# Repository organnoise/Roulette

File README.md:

# Roulette

Roulette is a generative sequencer that uses probability algorithms to create rhythmically varied drum patterns. Compositionally the intent of Roulette is to enable its user to program drum patterns in a dynamic fashion, as opposed to the static nature of typical sequential composition. From the initial design of a rhythm, varied patterns are emitted outlining a principal musical form

## CAD
CAD files for 3D printing and CNC-ing

## Arduino 
Arduino code for Teeny++ 2.0

## Eagle

Designs for both the module and the shield pcbs.

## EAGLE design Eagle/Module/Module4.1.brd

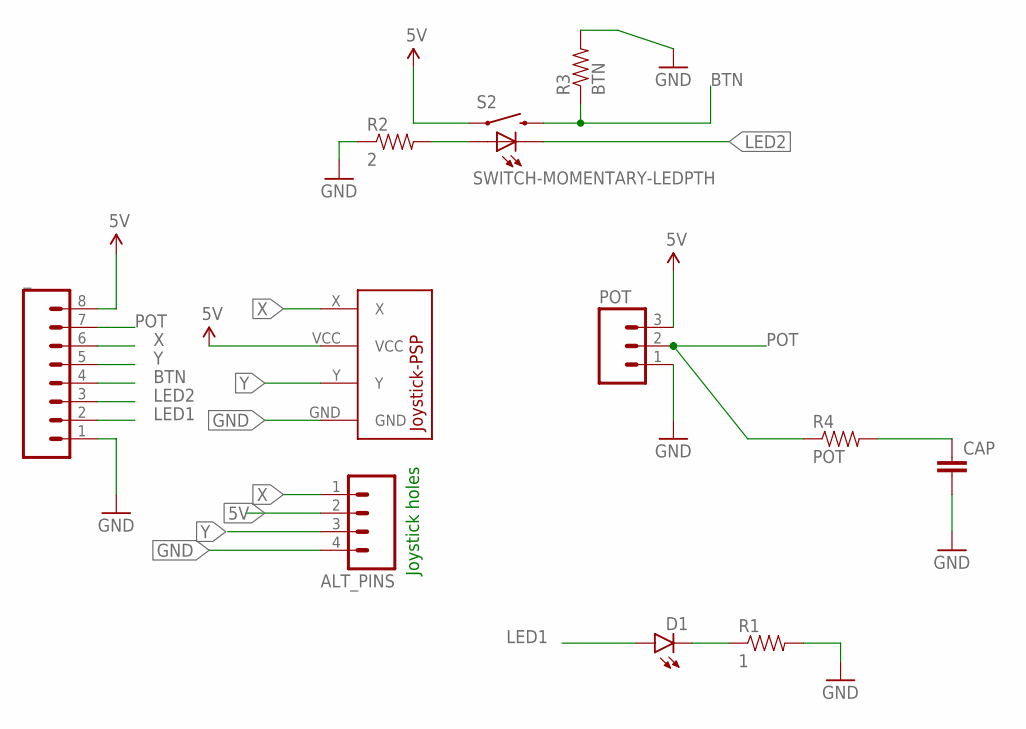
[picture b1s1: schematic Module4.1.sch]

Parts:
ALT_PINS: M04NO_SILK_ALL_ROUND; 1X04_NO_SILK_ALL_ROUND
CAP: CAPEZ; CAP-PTH-SMALLEZ
D1: LED3MM
POT: M031X03_NO_SILK; 1X03_NO_SILK
R1: 1; AXIAL-0.3-KIT
R2: 2; AXIAL-0.3-KIT
R3: BTN; AXIAL-0.3-KIT
R4: POT; AXIAL-0.3-KIT
S2: SWITCH-MOMENTARY-LEDPTH; TACTILE-PTH-LED-12MM
U$1: JOYSTICK-PSP1000
_: M08; 1X08_ROUND

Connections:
5V: ALT_PINS.2, POT.3, S2.4 (1), U$1.VCC, _.8
BTN: R3.P$1 (1), S2.2, _.4
GND: ALT_PINS.4, CAP.2, POT.1, R1.P$2 (2), R2.P$1 (1), R3.P$2 (2), U$1.GND, _.1
LED1: D1.A, _.2
LED2: S2.C, _.3
unnamed: D1.K (C), R1.P$1 (1)
unnamed: R2.P$2 (2), S2.A
unnamed: CAP.1, R4.P$2 (2)
POT: POT.2, R4.P$1 (1), _.7
X: ALT_PINS.1, U$1.X, _.6
Y: ALT_PINS.3, U$1.Y, _.5

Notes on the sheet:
Joystick holes

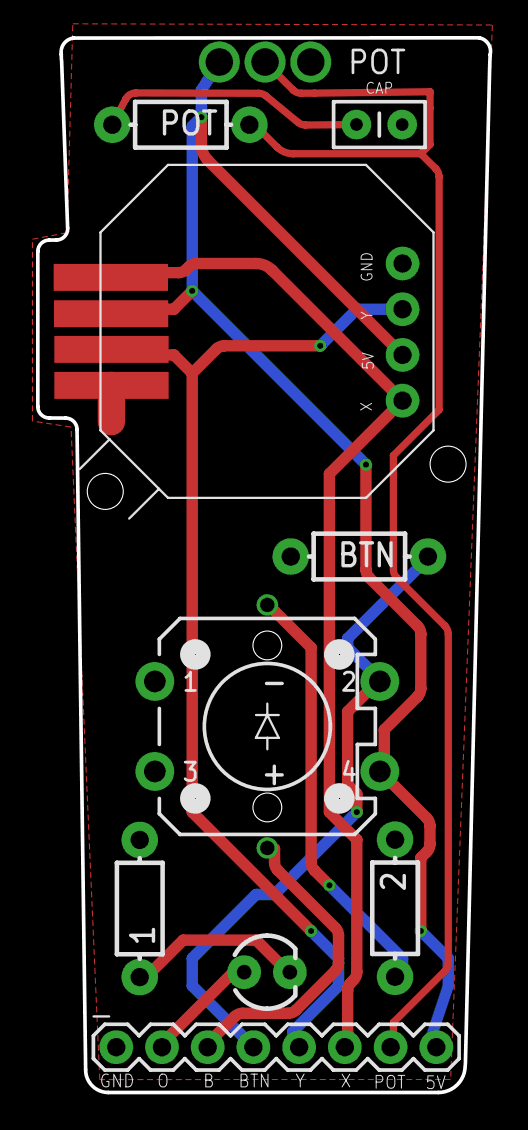
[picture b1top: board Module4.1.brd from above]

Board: 2 copper layers, 25.2 x 58.6 mm, 11 parts (0 on the bottom side), 11 nets.

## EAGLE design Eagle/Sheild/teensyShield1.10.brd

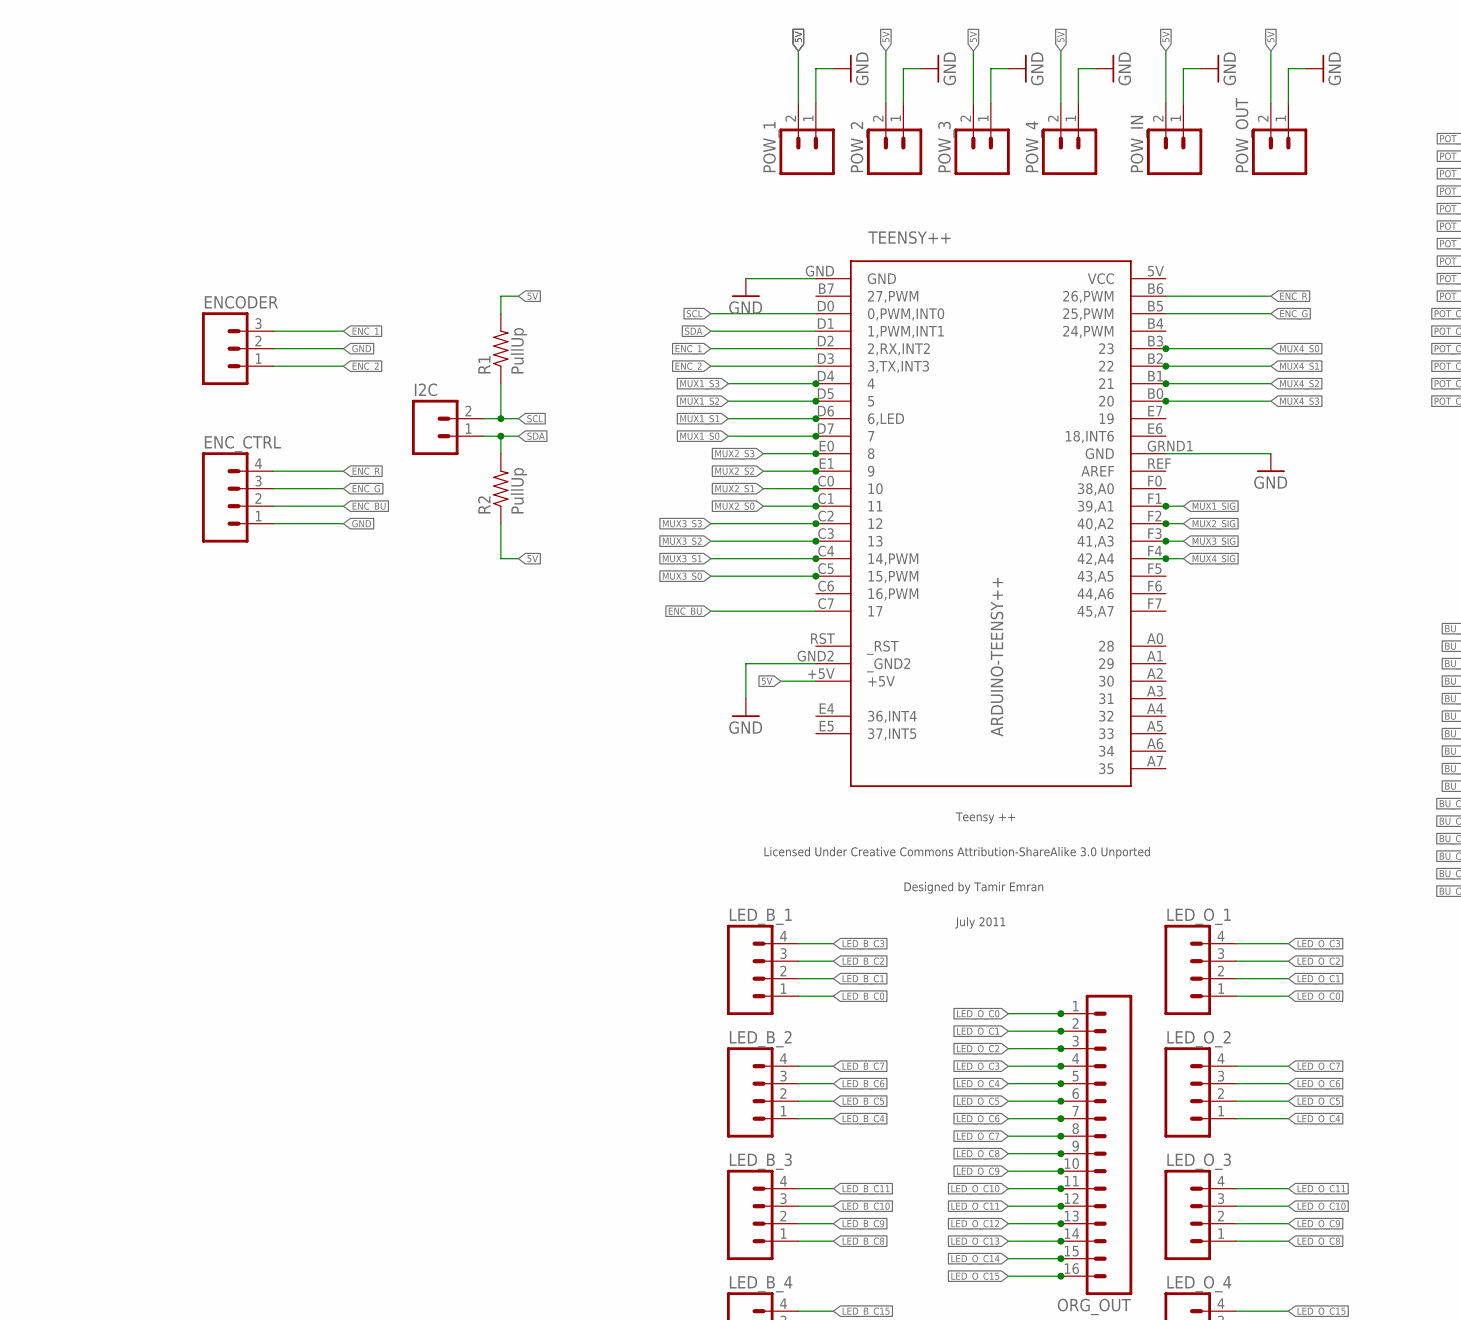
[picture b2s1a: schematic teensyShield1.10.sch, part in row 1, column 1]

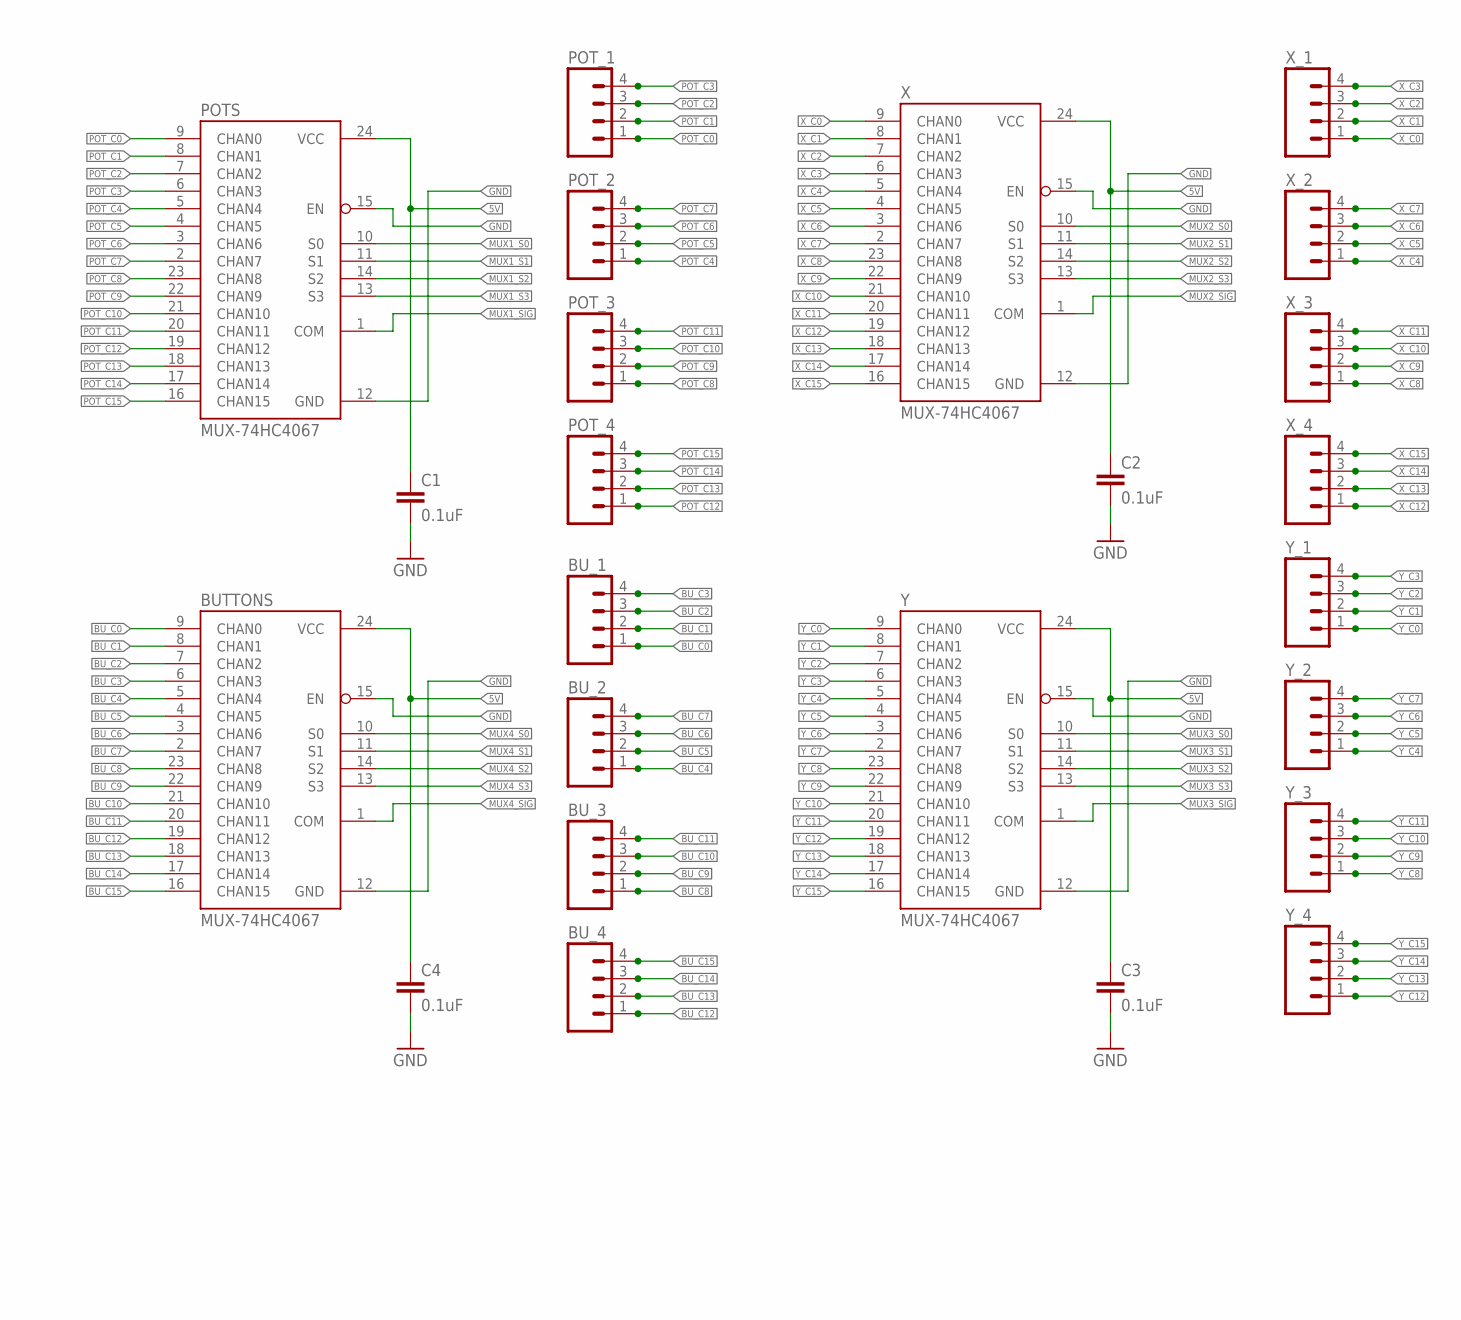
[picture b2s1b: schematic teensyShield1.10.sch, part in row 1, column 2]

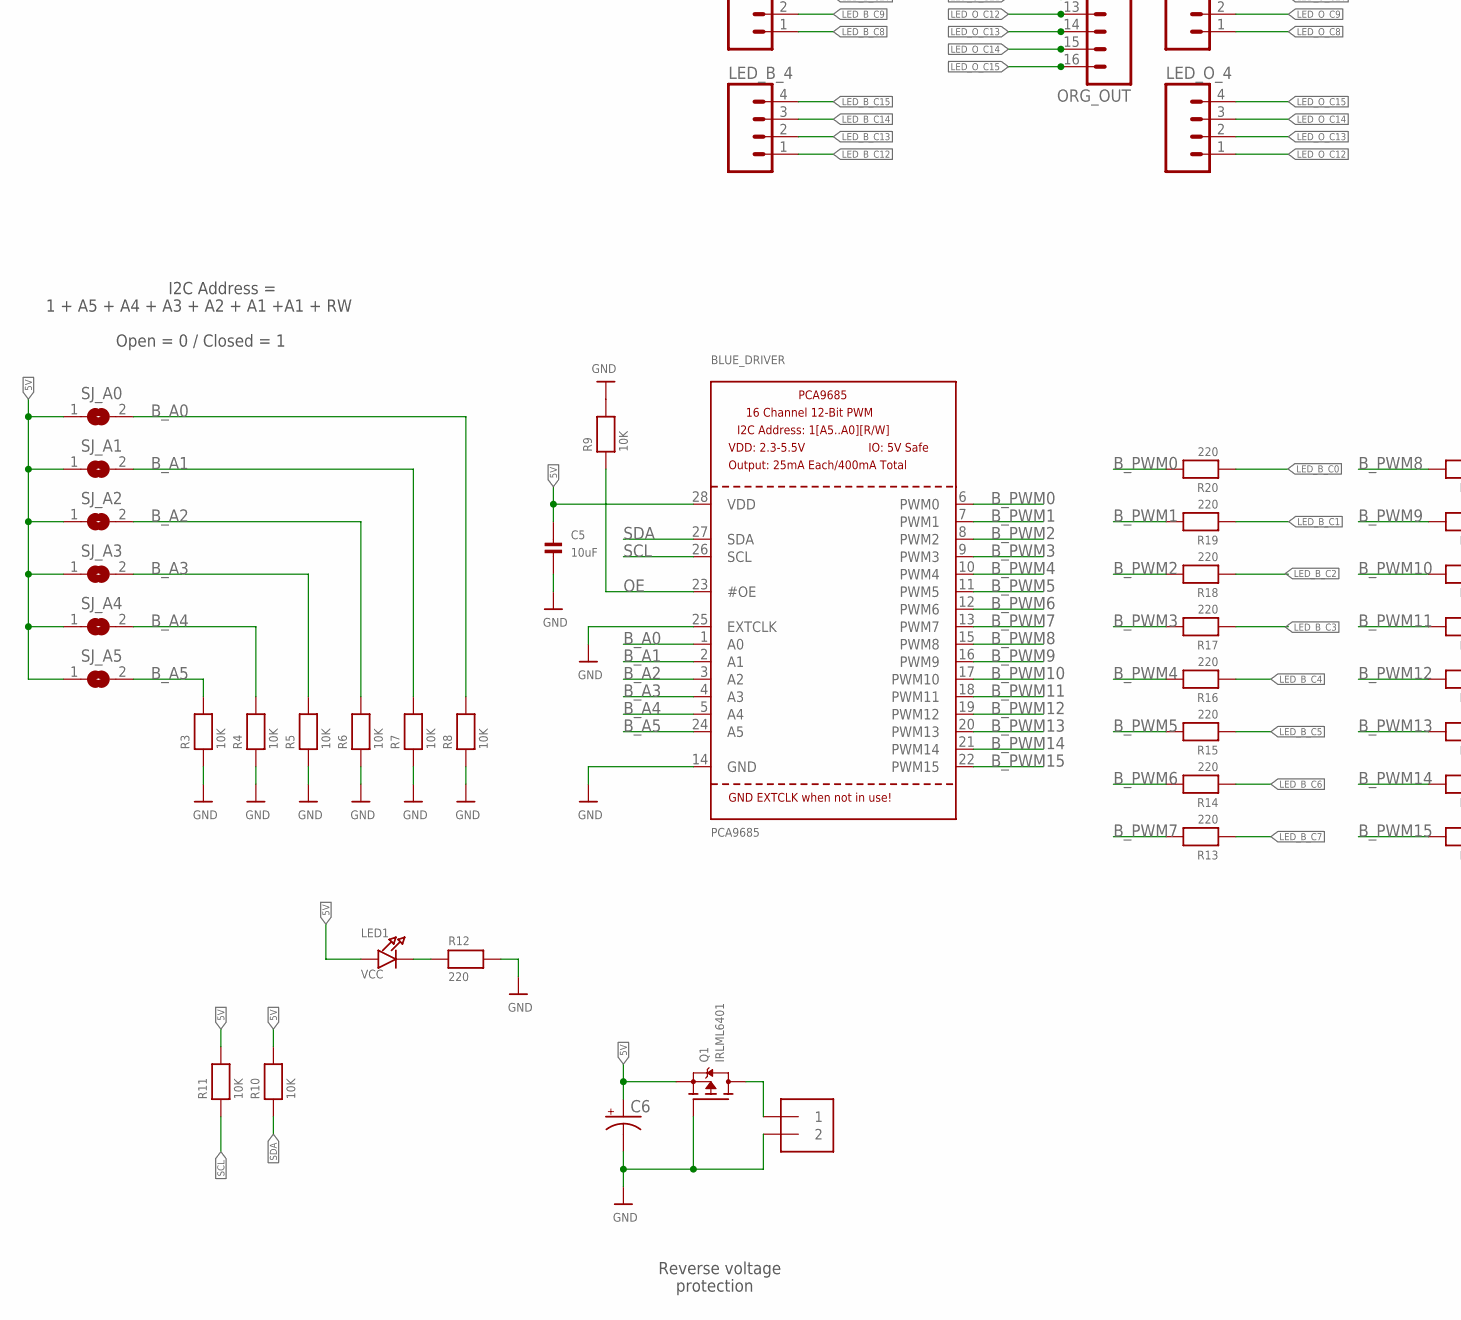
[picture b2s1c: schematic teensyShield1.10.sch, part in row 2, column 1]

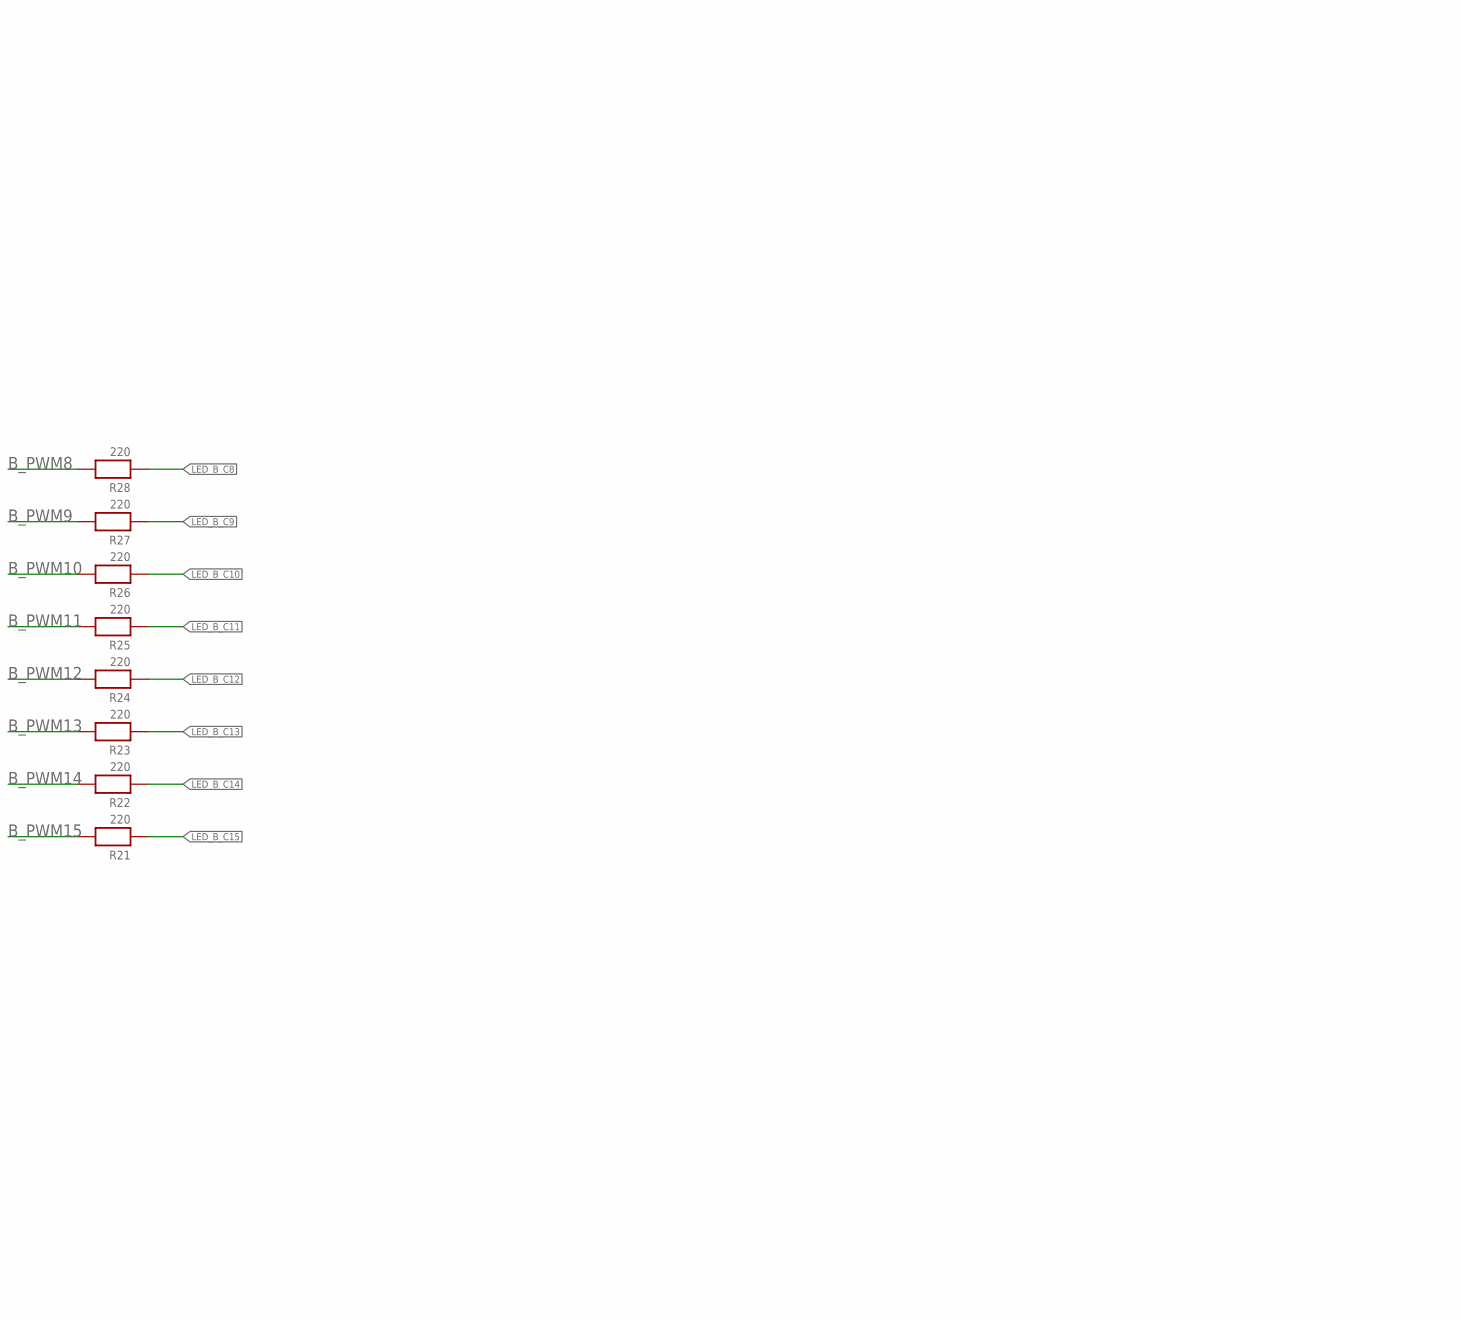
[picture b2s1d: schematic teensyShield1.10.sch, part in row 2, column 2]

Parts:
BLUE_DRIVER: PCA9685; TSSOP28
BUTTONS: MUX-74HC4067; SSOP24
BU_1, BU_2, BU_3, BU_4: M04NO_SILK_ALL_ROUND; 1X04_NO_SILK_ALL_ROUND
C1, C2, C3, C4: 0.1uF; 0603
C5: 10uF; 0805
C6: CPOL-USE3.5-8; E3,5-8
ENCODER: M031X03_NO_SILK; 1X03_NO_SILK
ENC_CTRL: M041X04_NO_SILK; 1X04_NO_SILK
I2C: M02LOCK; 1X02_LOCK
J1: TERMBLOCK_1X2-3.5MM; 1X2-3.5MM
LED1: VCC; CHIPLED_0805
LED_B_1, LED_B_2, LED_B_3, LED_B_4: M04NO_SILK_ALL_ROUND; 1X04_NO_SILK_ALL_ROUND
LED_O_1, LED_O_2, LED_O_3, LED_O_4: M04NO_SILK_ALL_ROUND; 1X04_NO_SILK_ALL_ROUND
ORG_OUT: M161X16_NO_SILK; 1X16_NO_SILK
POTS: MUX-74HC4067; SSOP24
POT_1, POT_2, POT_3, POT_4: M04NO_SILK_ALL_ROUND; 1X04_NO_SILK_ALL_ROUND
POW_1, POW_2, POW_3, POW_4: M02POLAR; MOLEX-1X2
POW_IN: M02POLAR; MOLEX-1X2
POW_OUT: M02POLAR; MOLEX-1X2
Q1: IRLML6401; SOT23-WIDE
R1, R2: PullUp; AXIAL-0.3
R3, R4, R5, R6, R7, R8, R9, R10, R11: 10K; 0805
R12, R13, R14, R15, R16, R17, R18, R19, R20, R21, R22, R23, R24, R25, R26, R27, R28: 220; 0805
SJ_A0, SJ_A1, SJ_A2, SJ_A3, SJ_A4, SJ_A5: SOLDERJUMPERREFLOW_NOPASTE; SOLDERJUMPER_REFLOW_NOPASTE
TEENSY++: ARDUINO-TEENSY++; TEENSY++
X: MUX-74HC4067; SSOP24
X_1, X_2, X_3, X_4: M04NO_SILK_ALL_ROUND; 1X04_NO_SILK_ALL_ROUND
Y: MUX-74HC4067; SSOP24
Y_1, Y_2, Y_3, Y_4: M04NO_SILK_ALL_ROUND; 1X04_NO_SILK_ALL_ROUND

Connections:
5V: BLUE_DRIVER.28 (VDD), BUTTONS.24 (VCC), C1.1, C2.1, C3.1, C4.1, C5.1, C6.+, LED1.A, POTS.24 (VCC), POW_1.2, POW_2.2, POW_3.2, POW_4.2, POW_IN.2, POW_OUT.2, Q1.2 (S), R1.P$2 (2), R2.P$1 (1), R10.2, R11.2, SJ_A0.1, SJ_A1.1, SJ_A2.1, SJ_A3.1, SJ_A4.1, SJ_A5.1, TEENSY++.+5V, X.24 (VCC), Y.24 (VCC)
BU_C0: BUTTONS.9 (CHAN0), BU_1.1
BU_C1: BUTTONS.8 (CHAN1), BU_1.2
BU_C2: BUTTONS.7 (CHAN2), BU_1.3
BU_C3: BUTTONS.6 (CHAN3), BU_1.4
BU_C4: BUTTONS.5 (CHAN4), BU_2.1
BU_C5: BUTTONS.4 (CHAN5), BU_2.2
BU_C6: BUTTONS.3 (CHAN6), BU_2.3
BU_C7: BUTTONS.2 (CHAN7), BU_2.4
BU_C8: BUTTONS.23 (CHAN8), BU_3.1
BU_C9: BUTTONS.22 (CHAN9), BU_3.2
BU_C10: BUTTONS.21 (CHAN10), BU_3.3
BU_C11: BUTTONS.20 (CHAN11), BU_3.4
BU_C12: BUTTONS.19 (CHAN12), BU_4.1
BU_C13: BUTTONS.18 (CHAN13), BU_4.2
BU_C14: BUTTONS.17 (CHAN14), BU_4.3
BU_C15: BUTTONS.16 (CHAN15), BU_4.4
B_A0: BLUE_DRIVER.1 (A0), R8.2, SJ_A0.2
B_A1: BLUE_DRIVER.2 (A1), R7.2, SJ_A1.2
B_A2: BLUE_DRIVER.3 (A2), R6.2, SJ_A2.2
B_A3: BLUE_DRIVER.4 (A3), R5.2, SJ_A3.2
B_A4: BLUE_DRIVER.5 (A4), R4.2, SJ_A4.2
B_A5: BLUE_DRIVER.24 (A5), R3.2, SJ_A5.2
B_PWM0: BLUE_DRIVER.6 (PWM0), R20.2
B_PWM1: BLUE_DRIVER.7 (PWM1), R19.2
B_PWM2: BLUE_DRIVER.8 (PWM2), R18.2
B_PWM3: BLUE_DRIVER.9 (PWM3), R17.2
B_PWM4: BLUE_DRIVER.10 (PWM4), R16.2
B_PWM5: BLUE_DRIVER.11 (PWM5), R15.2
B_PWM6: BLUE_DRIVER.12 (PWM6), R14.2
B_PWM7: BLUE_DRIVER.13 (PWM7), R13.2
B_PWM8: BLUE_DRIVER.15 (PWM8), R28.2
B_PWM9: BLUE_DRIVER.16 (PWM9), R27.2
B_PWM10: BLUE_DRIVER.17 (PWM10), R26.2
B_PWM11: BLUE_DRIVER.18 (PWM11), R25.2
B_PWM12: BLUE_DRIVER.19 (PWM12), R24.2
B_PWM13: BLUE_DRIVER.20 (PWM13), R23.2
B_PWM14: BLUE_DRIVER.21 (PWM14), R22.2
B_PWM15: BLUE_DRIVER.22 (PWM15), R21.2
ENC_1: ENCODER.3, TEENSY++.D2 (2,RX,INT2)
ENC_2: ENCODER.1, TEENSY++.D3 (3,TX,INT3)
ENC_BU: ENC_CTRL.2, TEENSY++.C7 (17)
ENC_G: ENC_CTRL.3, TEENSY++.B5 (25,PWM)
ENC_R: ENC_CTRL.4, TEENSY++.B6 (26,PWM)
GND: BLUE_DRIVER.14 (GND), BLUE_DRIVER.25 (EXTCLK), BUTTONS.12 (GND), BUTTONS.15 (EN), C1.2, C2.2, C3.2, C4.2, C5.2, C6.-, ENCODER.2, ENC_CTRL.1, J1.2, POTS.12 (GND), POTS.15 (EN), POW_1.1, POW_2.1, POW_3.1, POW_4.1, POW_IN.1, POW_OUT.1, Q1.1 (G), R3.1, R4.1, R5.1, R6.1, R7.1, R8.1, R9.2, R12.2, TEENSY++.GND, TEENSY++.GND2 (_GND2), TEENSY++.GRND1 (GND), X.12 (GND), X.15 (EN), Y.12 (GND), Y.15 (EN)
LED_B_C0: LED_B_1.1, R20.1
LED_B_C1: LED_B_1.2, R19.1
LED_B_C2: LED_B_1.3, R18.1
LED_B_C3: LED_B_1.4, R17.1
LED_B_C4: LED_B_2.1, R16.1
LED_B_C5: LED_B_2.2, R15.1
LED_B_C6: LED_B_2.3, R14.1
LED_B_C7: LED_B_2.4, R13.1
LED_B_C8: LED_B_3.1, R28.1
LED_B_C9: LED_B_3.2, R27.1
LED_B_C10: LED_B_3.3, R26.1
LED_B_C11: LED_B_3.4, R25.1
LED_B_C12: LED_B_4.1, R24.1
LED_B_C13: LED_B_4.2, R23.1
LED_B_C14: LED_B_4.3, R22.1
LED_B_C15: LED_B_4.4, R21.1
LED_O_C0: LED_O_1.1, ORG_OUT.1
LED_O_C1: LED_O_1.2, ORG_OUT.2
LED_O_C2: LED_O_1.3, ORG_OUT.3
LED_O_C3: LED_O_1.4, ORG_OUT.4
LED_O_C4: LED_O_2.1, ORG_OUT.5
LED_O_C5: LED_O_2.2, ORG_OUT.6
LED_O_C6: LED_O_2.3, ORG_OUT.7
LED_O_C7: LED_O_2.4, ORG_OUT.8
LED_O_C8: LED_O_3.1, ORG_OUT.9
LED_O_C9: LED_O_3.2, ORG_OUT.10
LED_O_C10: LED_O_3.3, ORG_OUT.11
LED_O_C11: LED_O_3.4, ORG_OUT.12
LED_O_C12: LED_O_4.1, ORG_OUT.13
LED_O_C13: LED_O_4.2, ORG_OUT.14
LED_O_C14: LED_O_4.3, ORG_OUT.15
LED_O_C15: LED_O_4.4, ORG_OUT.16
MUX1_S0: POTS.10 (S0), TEENSY++.D7 (7)
MUX1_S1: POTS.11 (S1), TEENSY++.D6 (6,LED)
MUX1_S2: POTS.14 (S2), TEENSY++.D5 (5)
MUX1_S3: POTS.13 (S3), TEENSY++.D4 (4)
MUX1_SIG: POTS.1 (COM), TEENSY++.F1 (39,A1)
MUX2_S0: TEENSY++.C1 (11), X.10 (S0)
MUX2_S1: TEENSY++.C0 (10), X.11 (S1)
MUX2_S2: TEENSY++.E1 (9), X.14 (S2)
MUX2_S3: TEENSY++.E0 (8), X.13 (S3)
MUX2_SIG: TEENSY++.F2 (40,A2), X.1 (COM)
MUX3_S0: TEENSY++.C5 (15,PWM), Y.10 (S0)
MUX3_S1: TEENSY++.C4 (14,PWM), Y.11 (S1)
MUX3_S2: TEENSY++.C3 (13), Y.14 (S2)
MUX3_S3: TEENSY++.C2 (12), Y.13 (S3)
MUX3_SIG: TEENSY++.F3 (41,A3), Y.1 (COM)
MUX4_S0: BUTTONS.10 (S0), TEENSY++.B3 (23)
MUX4_S1: BUTTONS.11 (S1), TEENSY++.B2 (22)
MUX4_S2: BUTTONS.14 (S2), TEENSY++.B1 (21)
MUX4_S3: BUTTONS.13 (S3), TEENSY++.B0 (20)
MUX4_SIG: BUTTONS.1 (COM), TEENSY++.F4 (42,A4)
unnamed: LED1.C, R12.1
OE: BLUE_DRIVER.23 (#OE), R9.1
POT_C0: POTS.9 (CHAN0), POT_1.1
POT_C1: POTS.8 (CHAN1), POT_1.2
POT_C2: POTS.7 (CHAN2), POT_1.3
POT_C3: POTS.6 (CHAN3), POT_1.4
POT_C4: POTS.5 (CHAN4), POT_2.1
POT_C5: POTS.4 (CHAN5), POT_2.2
POT_C6: POTS.3 (CHAN6), POT_2.3
POT_C7: POTS.2 (CHAN7), POT_2.4
POT_C8: POTS.23 (CHAN8), POT_3.1
POT_C9: POTS.22 (CHAN9), POT_3.2
POT_C10: POTS.21 (CHAN10), POT_3.3
POT_C11: POTS.20 (CHAN11), POT_3.4
POT_C12: POTS.19 (CHAN12), POT_4.1
POT_C13: POTS.18 (CHAN13), POT_4.2
POT_C14: POTS.17 (CHAN14), POT_4.3
POT_C15: POTS.16 (CHAN15), POT_4.4
PWRIN: J1.1, Q1.3 (D)
SCL: BLUE_DRIVER.26 (SCL), I2C.2, R1.P$1 (1), R11.1, TEENSY++.D0 (0,PWM,INT0)
SDA: BLUE_DRIVER.27 (SDA), I2C.1, R2.P$2 (2), R10.1, TEENSY++.D1 (1,PWM,INT1)
VCC: TEENSY++.5V (VCC)
X_C0: X.9 (CHAN0), X_1.1
X_C1: X.8 (CHAN1), X_1.2
X_C2: X.7 (CHAN2), X_1.3
X_C3: X.6 (CHAN3), X_1.4
X_C4: X.5 (CHAN4), X_2.1
X_C5: X.4 (CHAN5), X_2.2
X_C6: X.3 (CHAN6), X_2.3
X_C7: X.2 (CHAN7), X_2.4
X_C8: X.23 (CHAN8), X_3.1
X_C9: X.22 (CHAN9), X_3.2
X_C10: X.21 (CHAN10), X_3.3
X_C11: X.20 (CHAN11), X_3.4
X_C12: X.19 (CHAN12), X_4.1
X_C13: X.18 (CHAN13), X_4.2
X_C14: X.17 (CHAN14), X_4.3
X_C15: X.16 (CHAN15), X_4.4
Y_C0: Y.9 (CHAN0), Y_1.1
Y_C1: Y.8 (CHAN1), Y_1.2
Y_C2: Y.7 (CHAN2), Y_1.3
Y_C3: Y.6 (CHAN3), Y_1.4
Y_C4: Y.5 (CHAN4), Y_2.1
Y_C5: Y.4 (CHAN5), Y_2.2
Y_C6: Y.3 (CHAN6), Y_2.3
Y_C7: Y.2 (CHAN7), Y_2.4
Y_C8: Y.23 (CHAN8), Y_3.1
Y_C9: Y.22 (CHAN9), Y_3.2
Y_C10: Y.21 (CHAN10), Y_3.3
Y_C11: Y.20 (CHAN11), Y_3.4
Y_C12: Y.19 (CHAN12), Y_4.1
Y_C13: Y.18 (CHAN13), Y_4.2
Y_C14: Y.17 (CHAN14), Y_4.3
Y_C15: Y.16 (CHAN15), Y_4.4

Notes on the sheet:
Reverse voltage
protection
1 + A5 + A4 + A3 + A2 + A1 +A1 + RW
I2C Address =
Open = 0 / Closed = 1

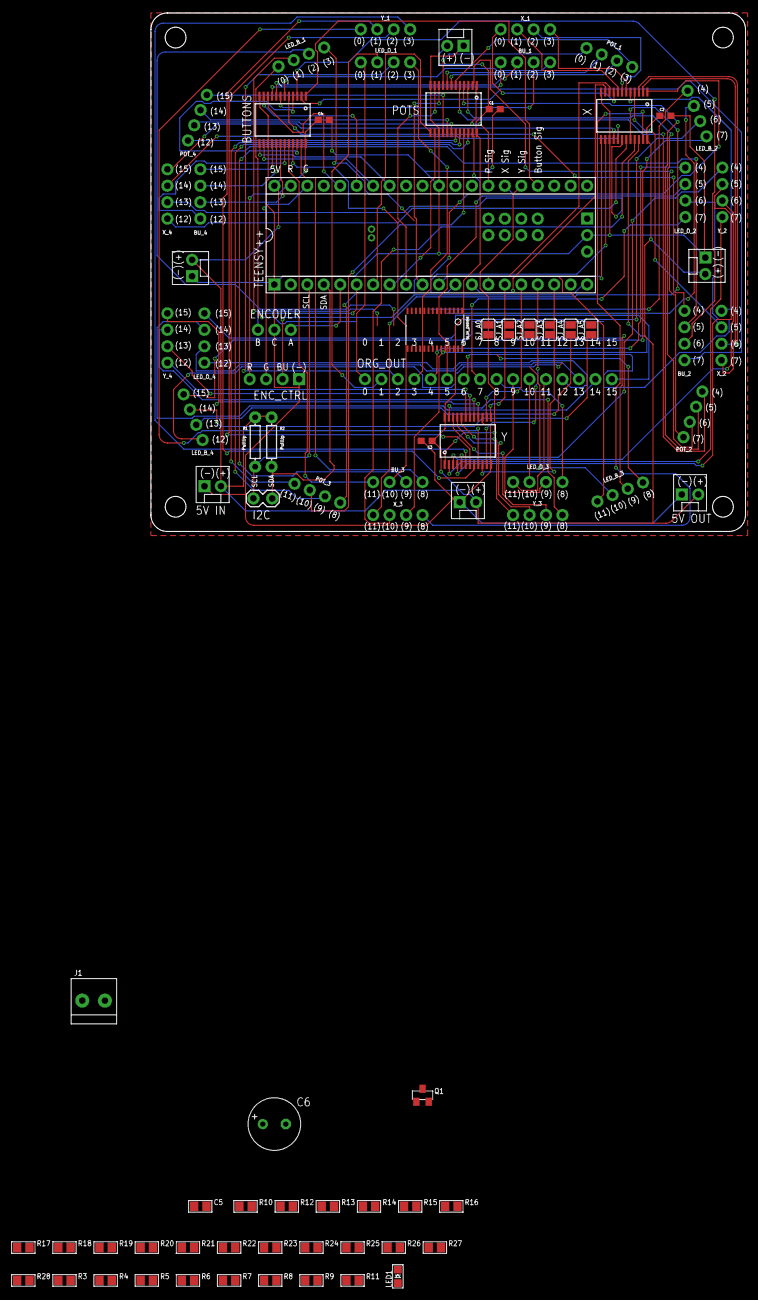
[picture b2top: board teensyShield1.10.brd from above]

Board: 2 copper layers, 91.7 x 80.0 mm, 83 parts (0 on the bottom side), 150 nets.

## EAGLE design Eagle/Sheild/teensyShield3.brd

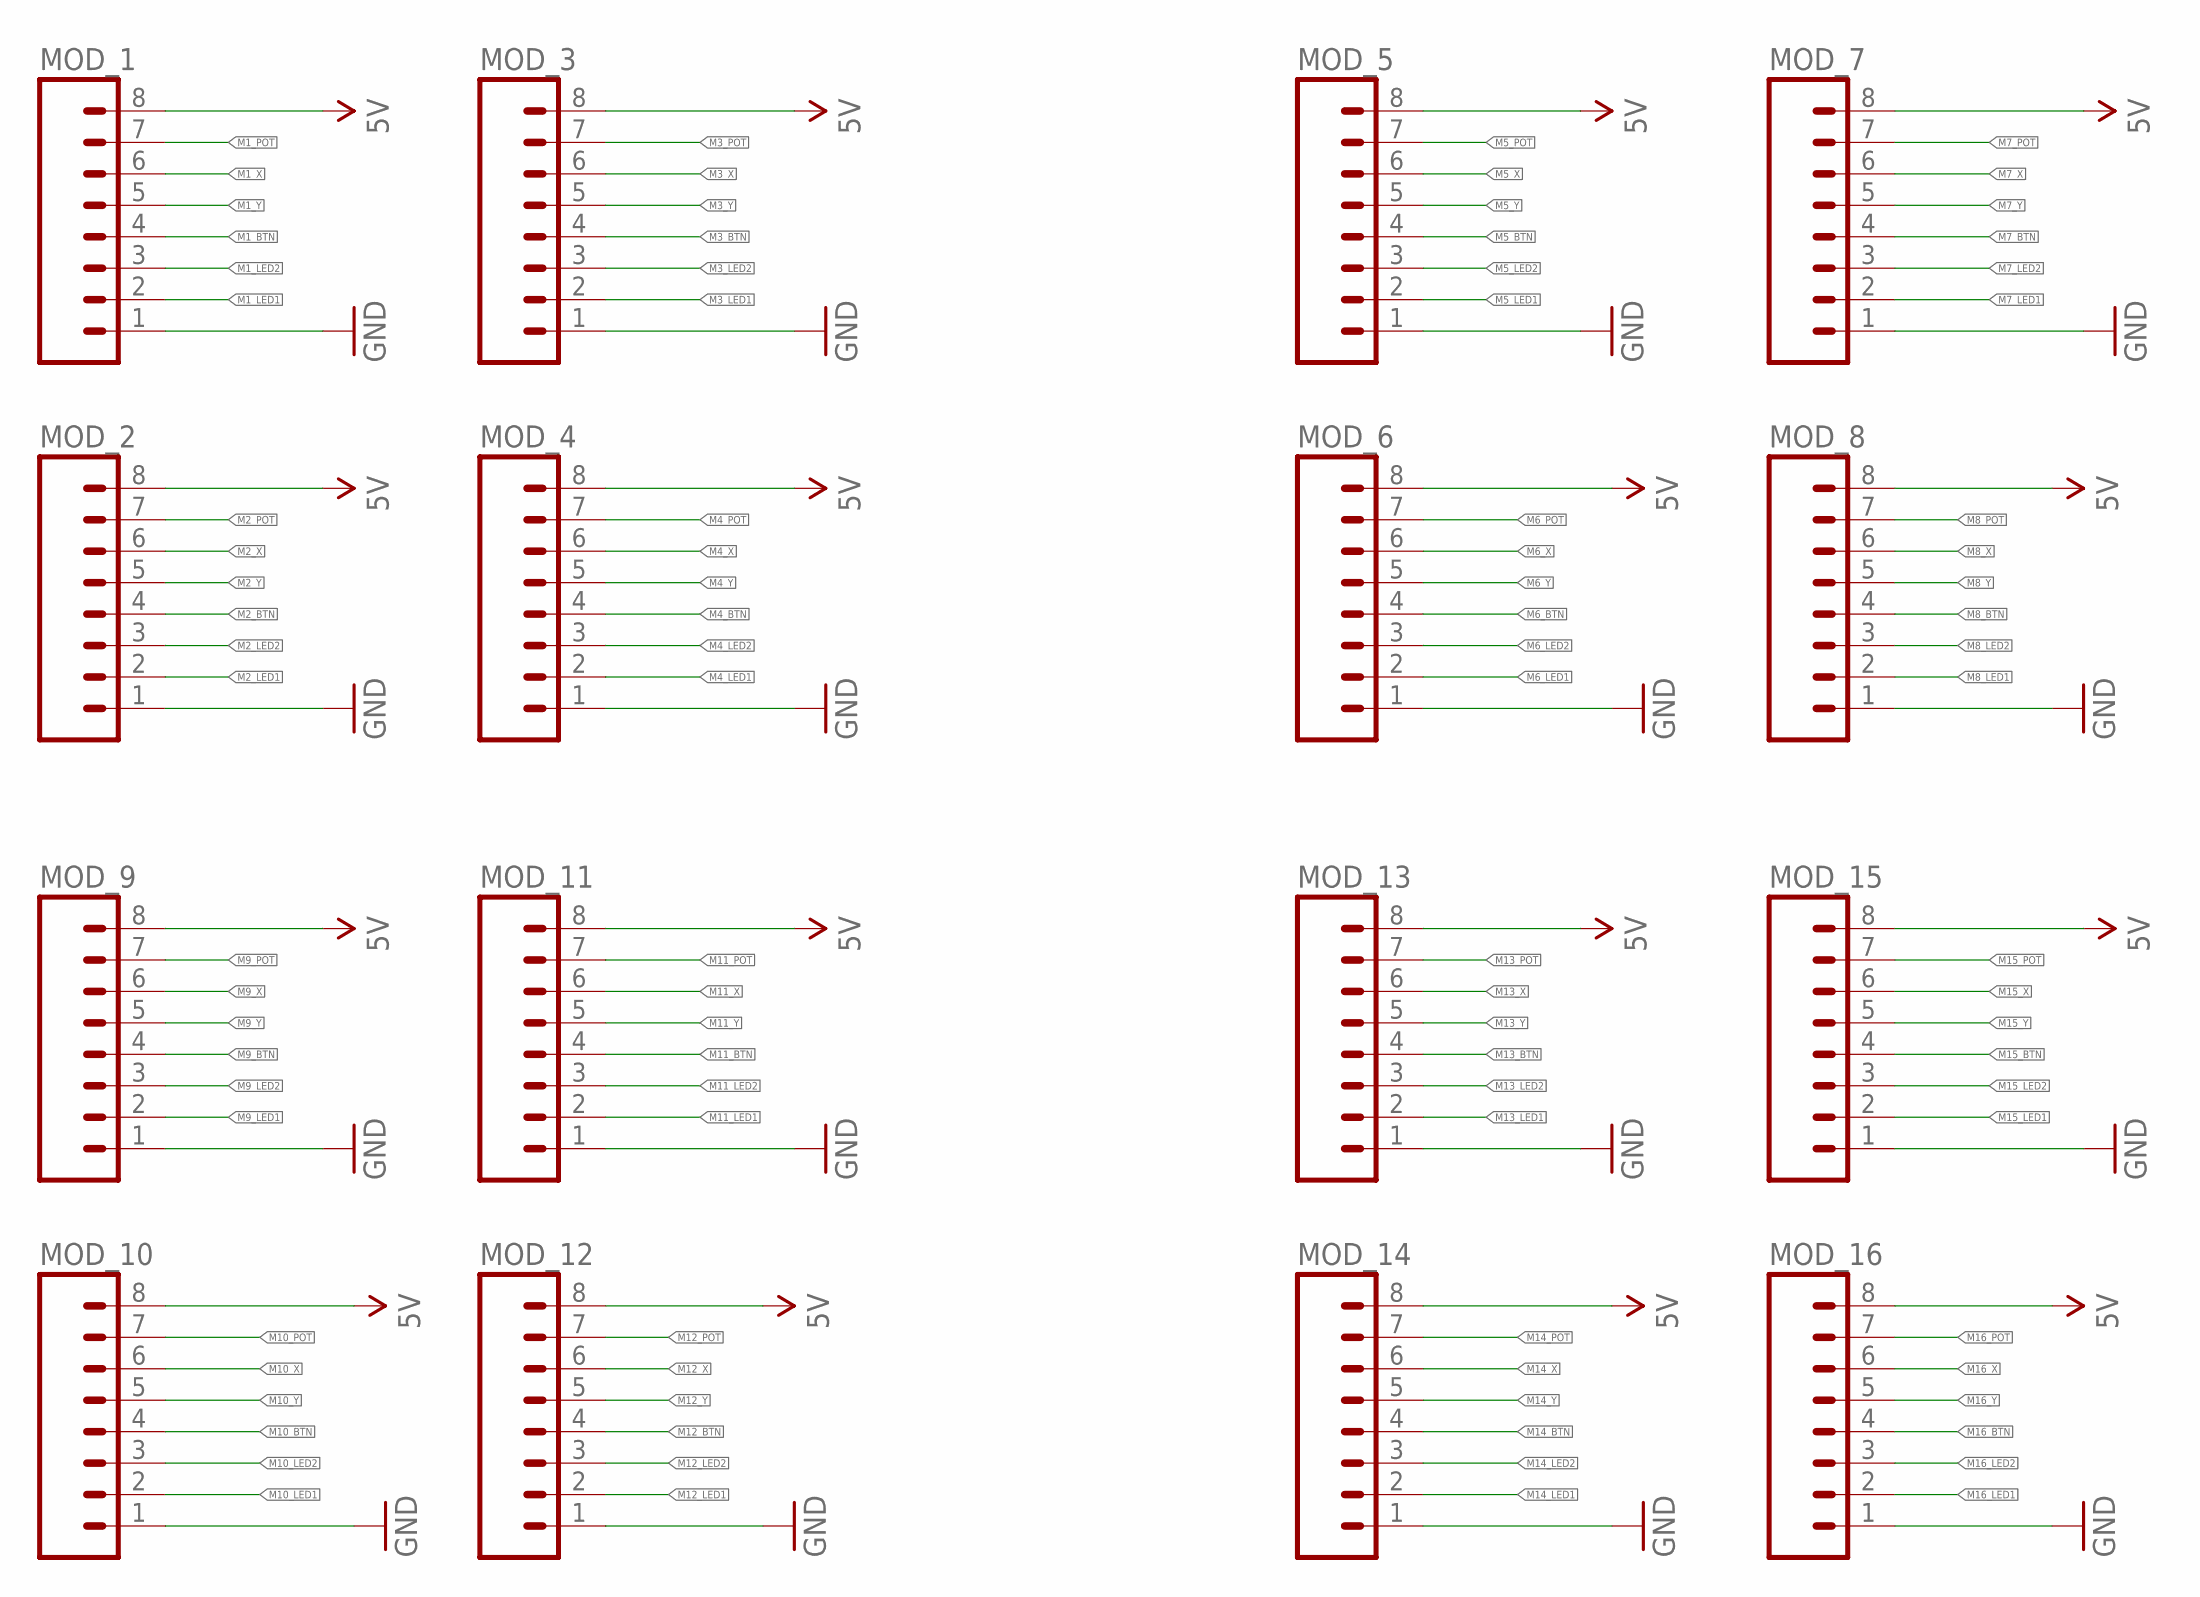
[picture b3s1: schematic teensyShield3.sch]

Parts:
MOD_1, MOD_2, MOD_3, MOD_4, MOD_5, MOD_6, MOD_7, MOD_8, MOD_9, MOD_10, MOD_11, MOD_12, MOD_13, MOD_14, MOD_15, MOD_16: M08; 1X08_ROUND

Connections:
M1_BTN1: MOD_11.4
M1_BTN2: MOD_3.4
M1_BTN3: MOD_7.4
M1_BTN6: MOD_8.4
M1_LED3: MOD_11.3
M1_LED4: MOD_11.2
M1_LED5: MOD_3.3
M1_LED6: MOD_3.2
M1_LED7: MOD_7.3
M1_LED8: MOD_7.2
M1_LED13: MOD_8.3
M1_LED14: MOD_8.2
M1_POT1: MOD_11.7
M1_POT2: MOD_3.7
M1_POT3: MOD_7.7
M1_POT6: MOD_8.7
M1_X1: MOD_11.6
M1_X2: MOD_3.6
M1_X3: MOD_7.6
M1_X6: MOD_8.6
M1_Y1: MOD_11.5
M1_Y2: MOD_3.5
M1_Y3: MOD_7.5
M1_Y6: MOD_8.5
M2_BTN: MOD_14.4
M2_BTN1: MOD_10.4
M2_BTN2: MOD_2.4
M2_BTN3: MOD_6.4
M2_BTN4: MOD_15.4
M2_LED1: MOD_14.2
M2_LED2: MOD_14.3
M2_LED3: MOD_10.3
M2_LED4: MOD_10.2
M2_LED5: MOD_2.3
M2_LED6: MOD_2.2
M2_LED7: MOD_6.3
M2_LED8: MOD_6.2
M2_LED9: MOD_15.3
M2_LED10: MOD_15.2
M2_POT: MOD_14.7
M2_POT1: MOD_10.7
M2_POT2: MOD_2.7
M2_POT3: MOD_6.7
M2_POT4: MOD_15.7
M2_X: MOD_14.6
M2_X1: MOD_10.6
M2_X2: MOD_2.6
M2_X3: MOD_6.6
M2_X4: MOD_15.6
M2_Y: MOD_14.5
M2_Y1: MOD_10.5
M2_Y2: MOD_2.5
M2_Y3: MOD_6.5
M2_Y4: MOD_15.5
M3_BTN: MOD_13.4
M3_BTN1: MOD_9.4
M3_BTN2: MOD_1.4
M3_BTN3: MOD_5.4
M3_LED1: MOD_13.2
M3_LED2: MOD_13.3
M3_LED3: MOD_9.3
M3_LED4: MOD_9.2
M3_LED5: MOD_1.3
M3_LED6: MOD_1.2
M3_LED7: MOD_5.3
M3_LED8: MOD_5.2
M3_POT: MOD_13.7
M3_POT1: MOD_9.7
M3_POT2: MOD_1.7
M3_POT3: MOD_5.7
M3_X: MOD_13.6
M3_X1: MOD_9.6
M3_X2: MOD_1.6
M3_X3: MOD_5.6
M3_Y: MOD_13.5
M3_Y1: MOD_9.5
M3_Y2: MOD_1.5
M3_Y3: MOD_5.5
M4_BTN: MOD_12.4
M4_BTN2: MOD_16.4
M4_BTN3: MOD_4.4
M4_LED1: MOD_12.2
M4_LED2: MOD_12.3
M4_LED5: MOD_16.3
M4_LED6: MOD_16.2
M4_LED7: MOD_4.3
M4_LED8: MOD_4.2
M4_POT: MOD_12.7
M4_POT2: MOD_16.7
M4_POT3: MOD_4.7
M4_X: MOD_12.6
M4_X2: MOD_16.6
M4_X3: MOD_4.6
M4_Y: MOD_12.5
M4_Y2: MOD_16.5
M4_Y3: MOD_4.5

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
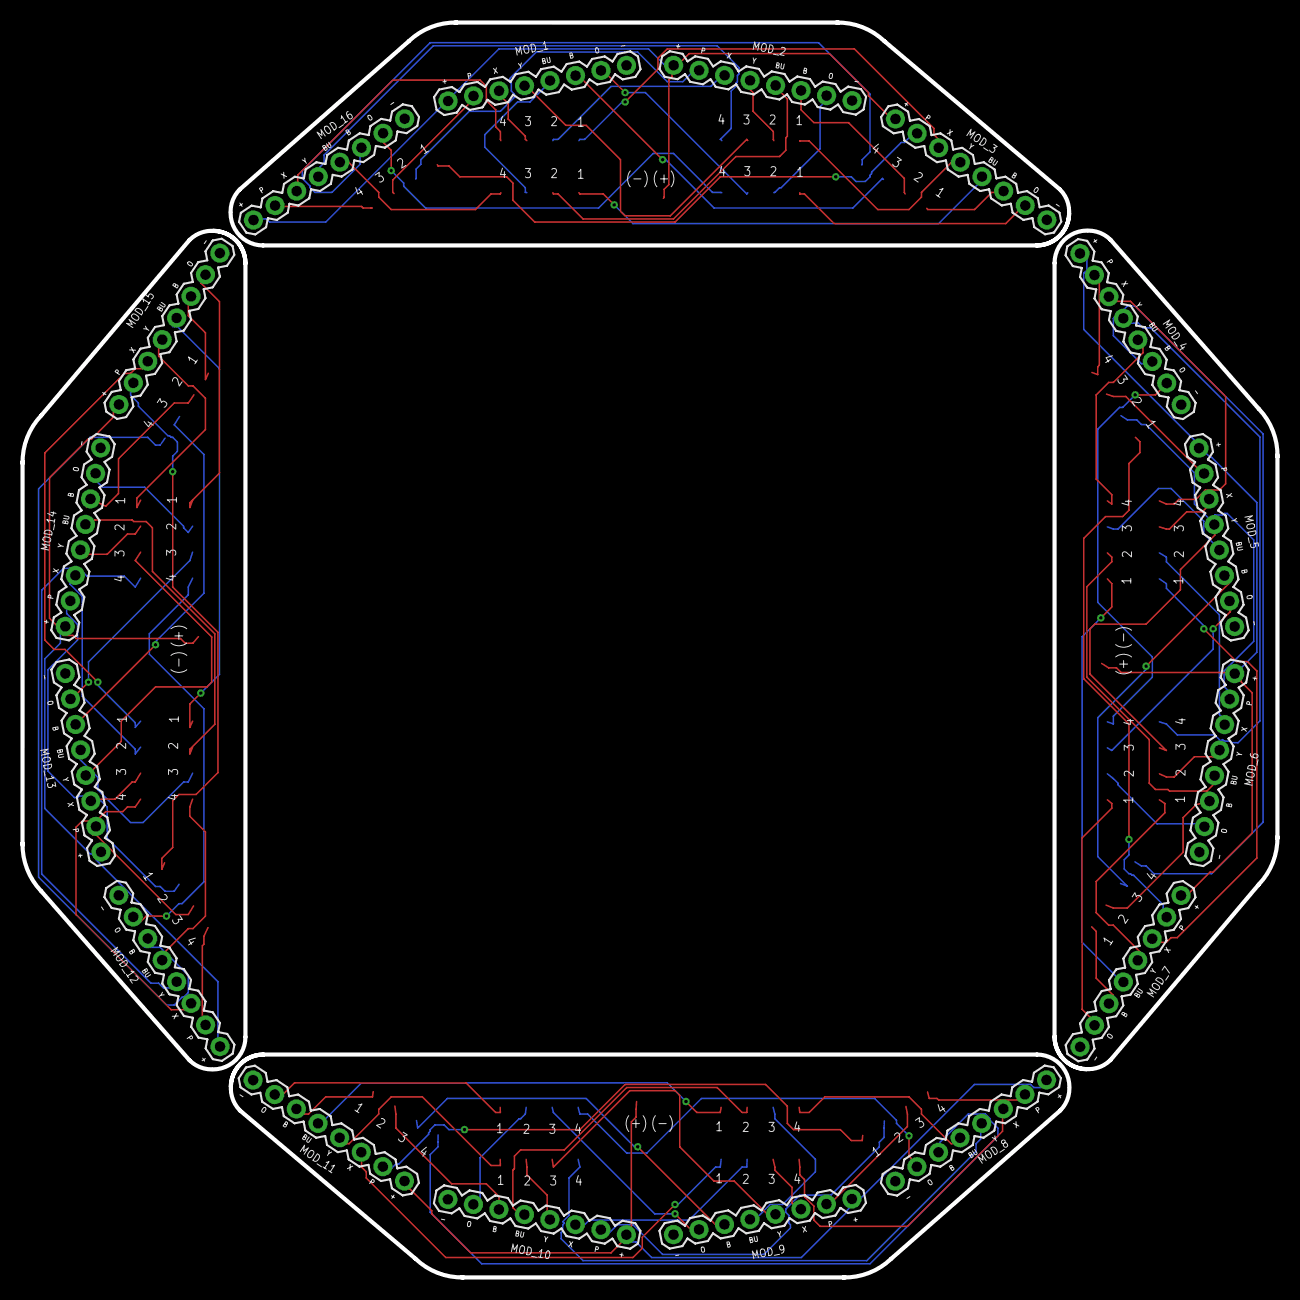
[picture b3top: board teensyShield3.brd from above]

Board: 2 copper layers, 122.6 x 122.6 mm, 16 parts (0 on the bottom side), 8 nets.

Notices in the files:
parts and their libraries:
SparkFun-LED: Licensing: Creative Commons ShareAlike 4.0 International - https://creativecommons.org/licenses/by-sa/4.0
teensypp: Licensed Under Creative Commons Attribution-ShareAlike 3.0 Unported
teensypp: Licensed Under Creative Commons Attribution-ShareAlike 3.0 Unported (CC BY-SA 3.0)
